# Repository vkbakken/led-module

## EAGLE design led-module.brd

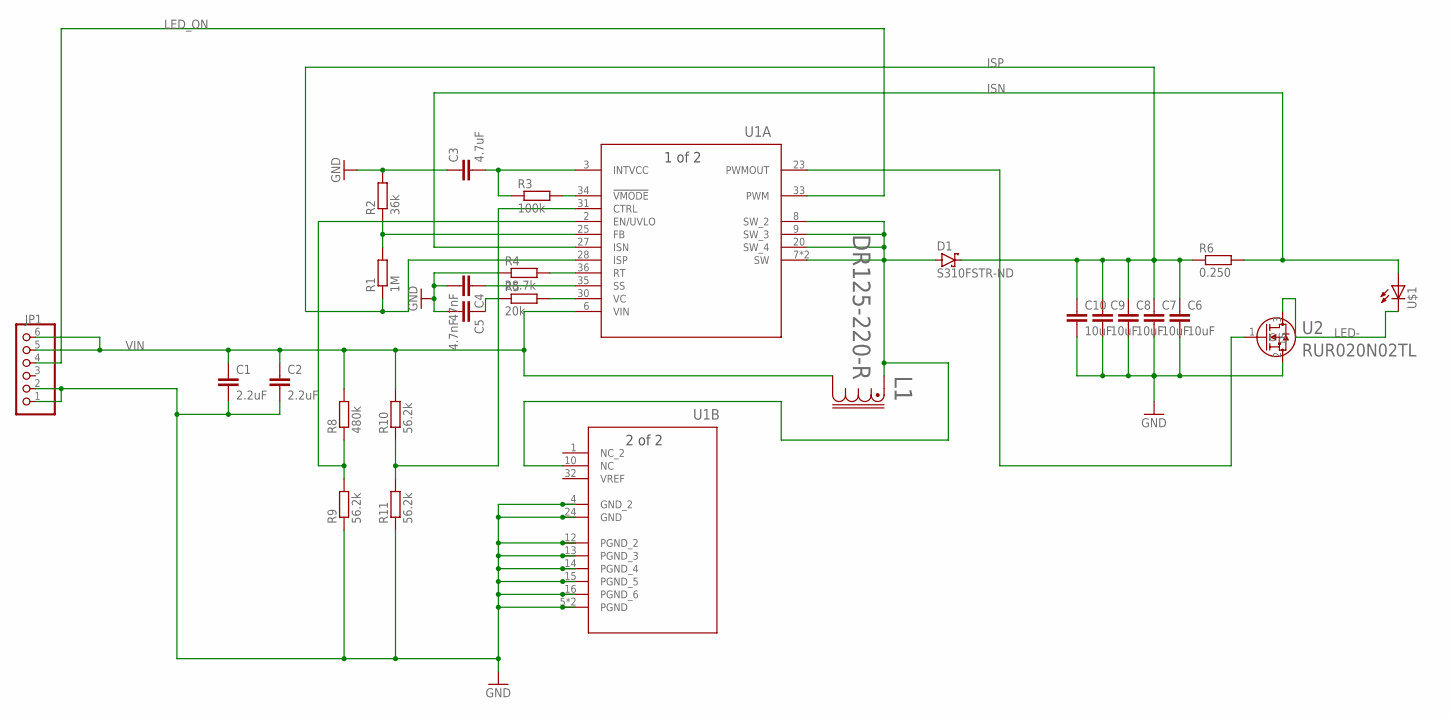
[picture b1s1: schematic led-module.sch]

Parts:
C1, C2: 2.2uF; C0805
C3: 4.7uF; C0402
C4: 47nF; C0402
C5: 4.7nF; C0402
C6, C7, C8, C9, C10: 10uF; C0805
D1: S310FSTR-ND; SMC
JP1: PINHD-1X6; 1X06
L1: DR125-220-R; DR125
R1: 1M; R0402
R2: 36k; R0402
R3: 100k; R0402
R4: 28.7k; R0402
R5: 20k; R0402
R6: 0.250; WSC2515
R8: 480k; R0402
R9, R10, R11: 56.2k; R0402
U1: LT3956EUHEPBFUHE_36_ADI-M; UHE_36_ADI-M
U2: RUR020N02TL; TRANS_RTR020N_ROM
U$1: 5-2154874-3

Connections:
GND: C1.2, C2.2, C3.1, C4.2, C5.2, C6.2, C7.2, C8.2, C9.2, C10.2, JP1.1, JP1.2, R2.2, R4.1, R9.1, R11.1, U1.4 (GND_2), U1.5 (PGND), U1.12 (PGND_2), U1.13 (PGND_3), U1.14 (PGND_4), U1.15 (PGND_5), U1.16 (PGND_6), U1.17 (PGND), U1.24 (GND), U2.2 (S)
ISN: R6.2, U1.27 (ISN), U$1.P$1 (A)
ISP: C6.1, C7.1, C8.1, C9.1, C10.1, D1.C, R1.1, R6.1, U1.28 (ISP)
LED-: U2.3 (D), U$1.P$2 (C)
LED_ON: JP1.4, U1.33 (PWM)
unnamed: C3.2, R3.1, U1.3 (INTVCC)
unnamed: R1.2, R2.1, U1.25 (FB)
unnamed: R3.2, U1.34 (!VMODE)
unnamed: R4.2, U1.36 (RT)
unnamed: C4.1, U1.35 (SS)
unnamed: R5.2, U1.30 (VC)
unnamed: C5.1, R5.1
unnamed: U1.23 (PWMOUT), U2.1 (G)
unnamed: D1.A, L1.1, U1.7 (SW), U1.8 (SW_2), U1.9 (SW_3), U1.10 (NC), U1.20 (SW_4), U1.21 (SW)
unnamed: R8.1, R9.2, U1.2 (EN/UVLO)
unnamed: R10.1, R11.2, U1.31 (CTRL)
VIN: C1.1, C2.1, JP1.5, JP1.6, L1.2, R8.2, R10.2, U1.6 (VIN)

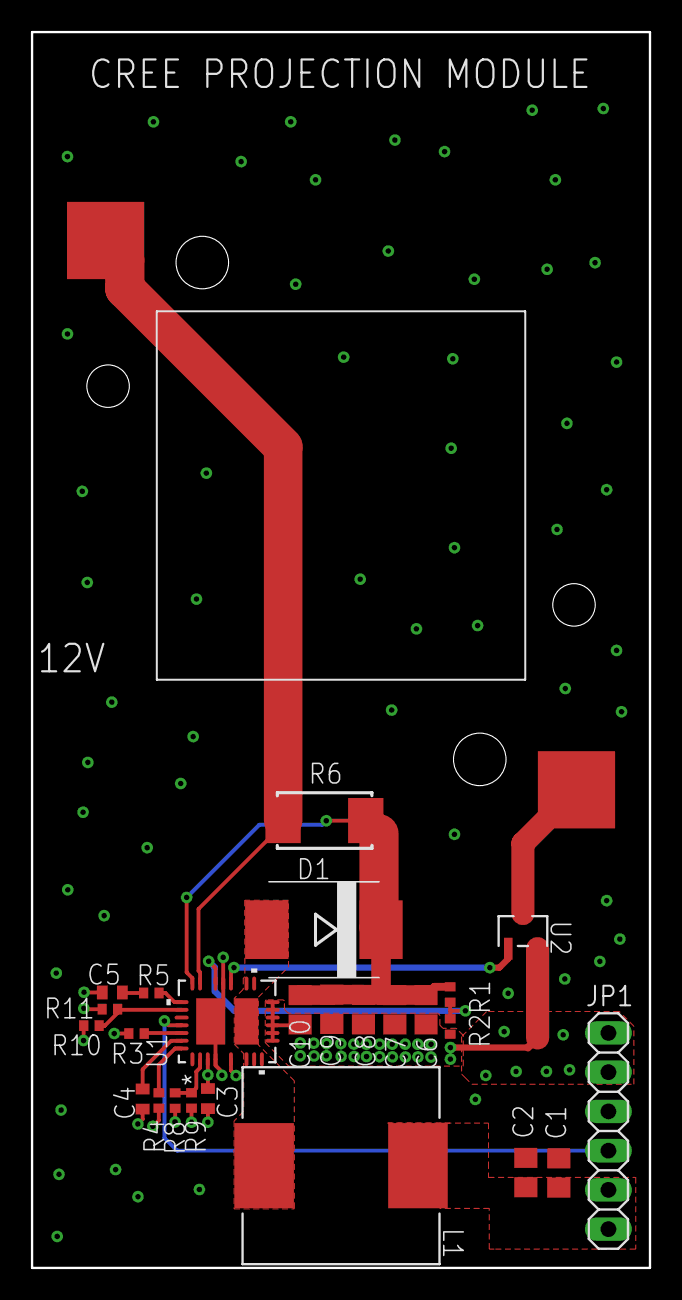
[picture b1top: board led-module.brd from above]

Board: 4 copper layers, 40.0 x 80.0 mm, 26 parts (0 on the bottom side), 17 nets.

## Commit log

2022-05-22 Initial
2022-05-22 Added libraries
2022-05-22 Layout wip
2022-08-07 Sent to production files

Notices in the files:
parts and their libraries:
COPYRIGHT: Copyright (C) 2021 Ultra Librarian. All rights reserved.
